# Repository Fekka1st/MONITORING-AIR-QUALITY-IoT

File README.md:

# Monitoring Air Quality and Smoke Emissions at Urban Bus Stops
_Ini adalah sebuah proyek untuk memonitoring kualitas udara di halte bus dengan menggunakan perangkat yaitu MQ135 dan juga MQ2 untuk mendeteksi ASAP_
_Sistem ini sudah integrasi dengan bylnk jadi kita bisa memantau melalui aplikasi tersebut untuk melihat data_
<h1>Anggota Proyek: </h1>
<h4>1.Hamdi Sholahudin</h4>
<h4>2.Hendri Hananta Wahyu Wibowo</h4>
<h4>3.Abu Yazid Bustomi</h4>
<h4>4.Ferry Aditya Herman </h4>
<h4>5.Tu Bagus Dwi Fikri </h4>

## Gambar Hasil :
<h3>Dashboard Blynk</h3>
<p align="center"></p>
<h3>Mobile Blynk</h3>
<p align="center"></p>

<h3>Device Monitoring</h3>
<p align="center"></p>
<p align="center"></p>  
<p align="center"></p>  

## Fitur :
- Mendeteksi Emisi ASAP
- Mendeteksi Kualitas Udara
- Mendeteksi Temperatur dan juga Kelembapan
- Ada Respon Suara jika ada asap berlebih atau kebakaran
- Ada led indikator untuk melihat kualitas udara (Green, Yellow, Red)
- Mendeteksi Lokasi Prangkat

## Requirements Prangkat :
- MQ2
- MQ135
- DHT22
- ESP32
- Buzzer
- LED RGB
- GPS NEON 6

## Platform Yang digunakan:
- Blynk
- Arduino IDE
- Platform.io
  
## Contact :
-[GitHub](https://www.github.com/Fekka1st/)
-

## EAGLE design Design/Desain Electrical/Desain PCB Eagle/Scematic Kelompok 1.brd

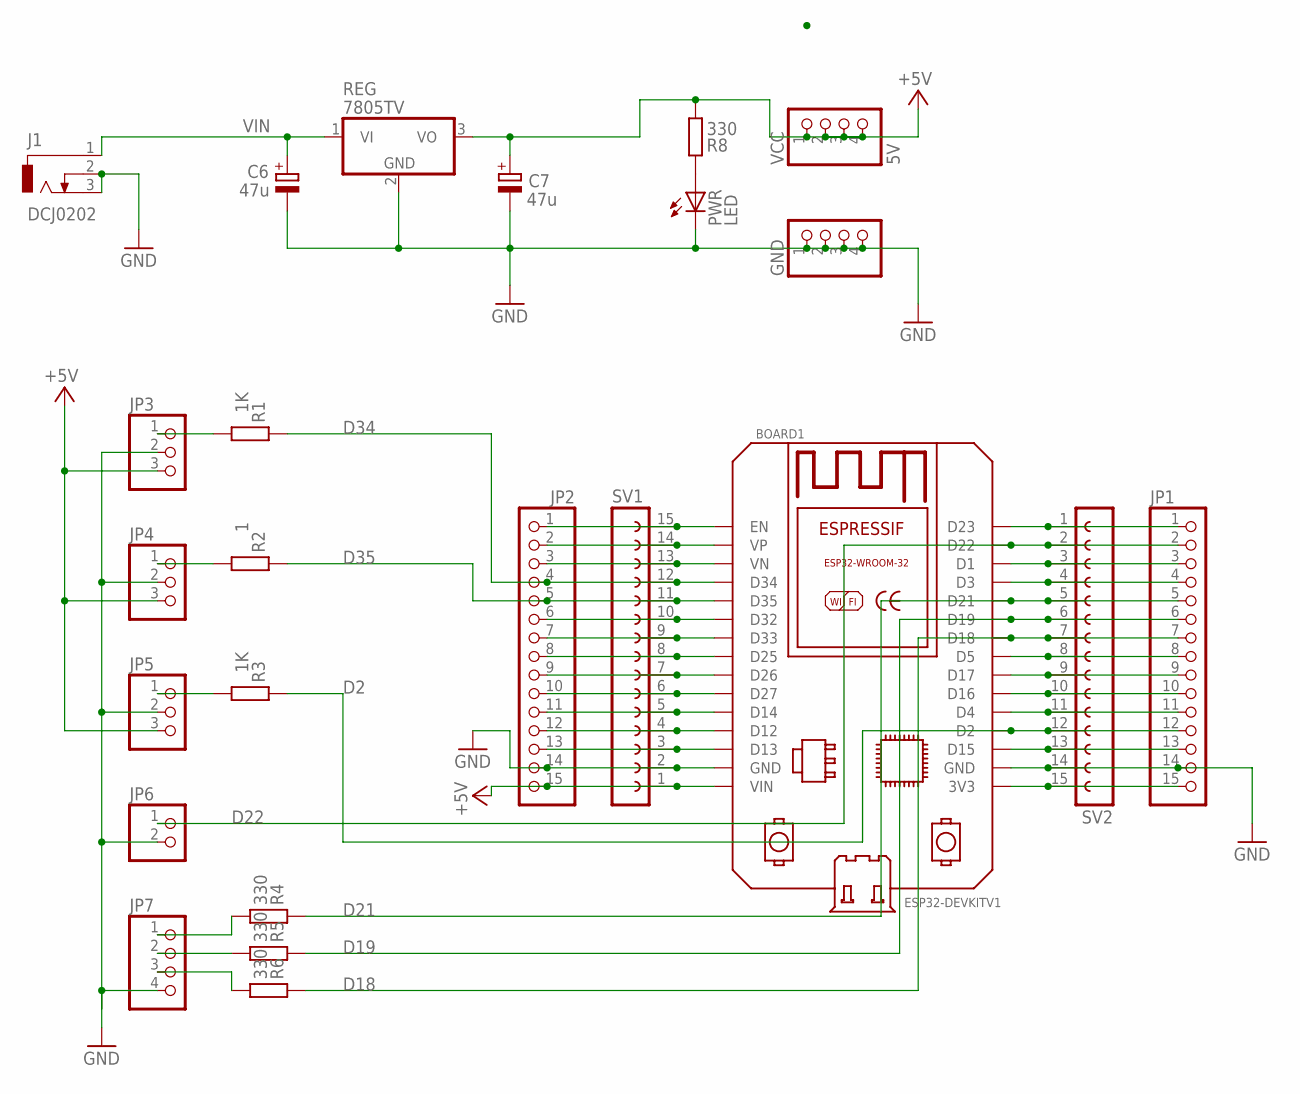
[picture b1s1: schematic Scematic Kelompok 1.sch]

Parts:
BOARD1: ESP32DEVKITV1SHRIDATTDUDHAT; ESP32-DEVKITV1
C6, C7: 47u; E2,5-5
GND: PINHD-1X4; 1X04
J1: DCJ0202
JP1, JP2: PINHD-1X15; 1X15
JP3, JP4, JP5: PINHD-1X3; 1X03
JP6: PINHD-1X2; 1X02
JP7: PINHD-1X4; 1X04
PWR: LED; LED3MM
R1, R3: 1K; 0204/7
R2: 1; 0204/7
R4, R5, R6, R8: 330; 0204/7
REG: 7805TV; TO220V
SV1, SV2: FE15-1; FE15
VCC: 5V; 1X04

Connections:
+5V: BOARD1.VIN, C7.+, JP2.15, JP3.3, JP4.3, JP5.3, R8.1, REG.3 (VO), SV1.1, VCC.1, VCC.2, VCC.3, VCC.4
D2: BOARD1.D2, JP1.12, R3.2, SV2.12
D18: BOARD1.D18, JP1.7, R6.2, SV2.7
D19: BOARD1.D19, JP1.6, R5.2, SV2.6
D21: BOARD1.D21, JP1.5, R4.2, SV2.5
D22: BOARD1.D22, JP1.2, JP6.1, SV2.2
D34: BOARD1.D34, JP2.4, R1.2, SV1.12
D35: BOARD1.D35, JP2.5, R2.2, SV1.11
GND: BOARD1.GND, BOARD1.GND@1 (GND), C6.-, C7.-, GND.1, GND.2, GND.3, GND.4, J1.2, J1.3, JP1.14, JP2.14, JP3.2, JP4.2, JP5.2, JP6.2, JP7.4, PWR.K (C), REG.2 (GND), SV1.2, SV2.14
unnamed: PWR.A, R8.2
unnamed: BOARD1.D26, JP2.9, SV1.7
unnamed: BOARD1.D33, BOARD1.EN, JP2.1, JP2.7, SV1.9, SV1.15
unnamed: BOARD1.VP, JP2.2, SV1.14
unnamed: BOARD1.VN, JP2.3, SV1.13
unnamed: BOARD1.D32, JP2.6, SV1.10
unnamed: BOARD1.D25, JP2.8, SV1.8
unnamed: BOARD1.D27, JP2.10, SV1.6
unnamed: BOARD1.D14, JP2.11, SV1.5
unnamed: BOARD1.D12, JP2.12, SV1.4
unnamed: BOARD1.D13, JP2.13, SV1.3
unnamed: JP3.1, R1.1
unnamed: BOARD1.D23, JP1.1, SV2.1
unnamed: BOARD1.D1, JP1.3, SV2.3
unnamed: BOARD1.D3, JP1.4, SV2.4
unnamed: BOARD1.D5, JP1.8, SV2.8
unnamed: BOARD1.D17, JP1.9, SV2.9
unnamed: BOARD1.D16, JP1.10, SV2.10
unnamed: BOARD1.D4, JP1.11, SV2.11
unnamed: BOARD1.D15, JP1.13, SV2.13
unnamed: JP4.1, R2.1
unnamed: BOARD1.3V3, JP1.15, SV2.15
unnamed: JP5.1, R3.1
unnamed: JP7.1, R4.1
unnamed: JP7.2, R5.1
unnamed: JP7.3, R6.1
VIN: C6.+, J1.1, REG.1 (VI)

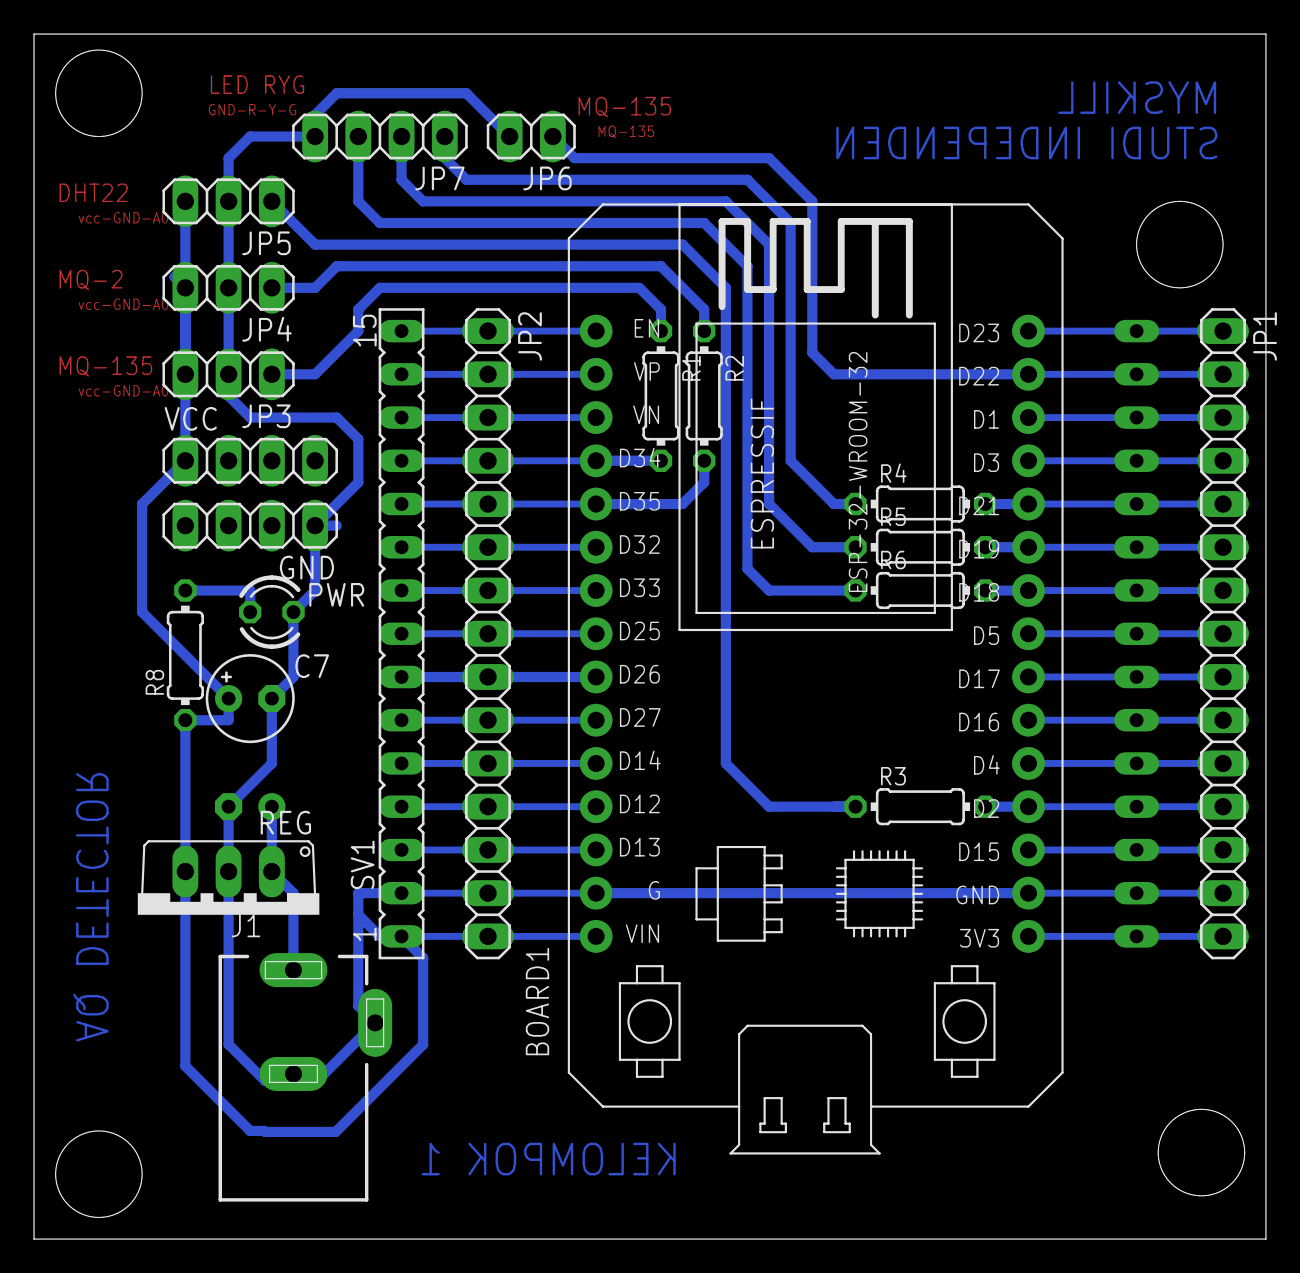
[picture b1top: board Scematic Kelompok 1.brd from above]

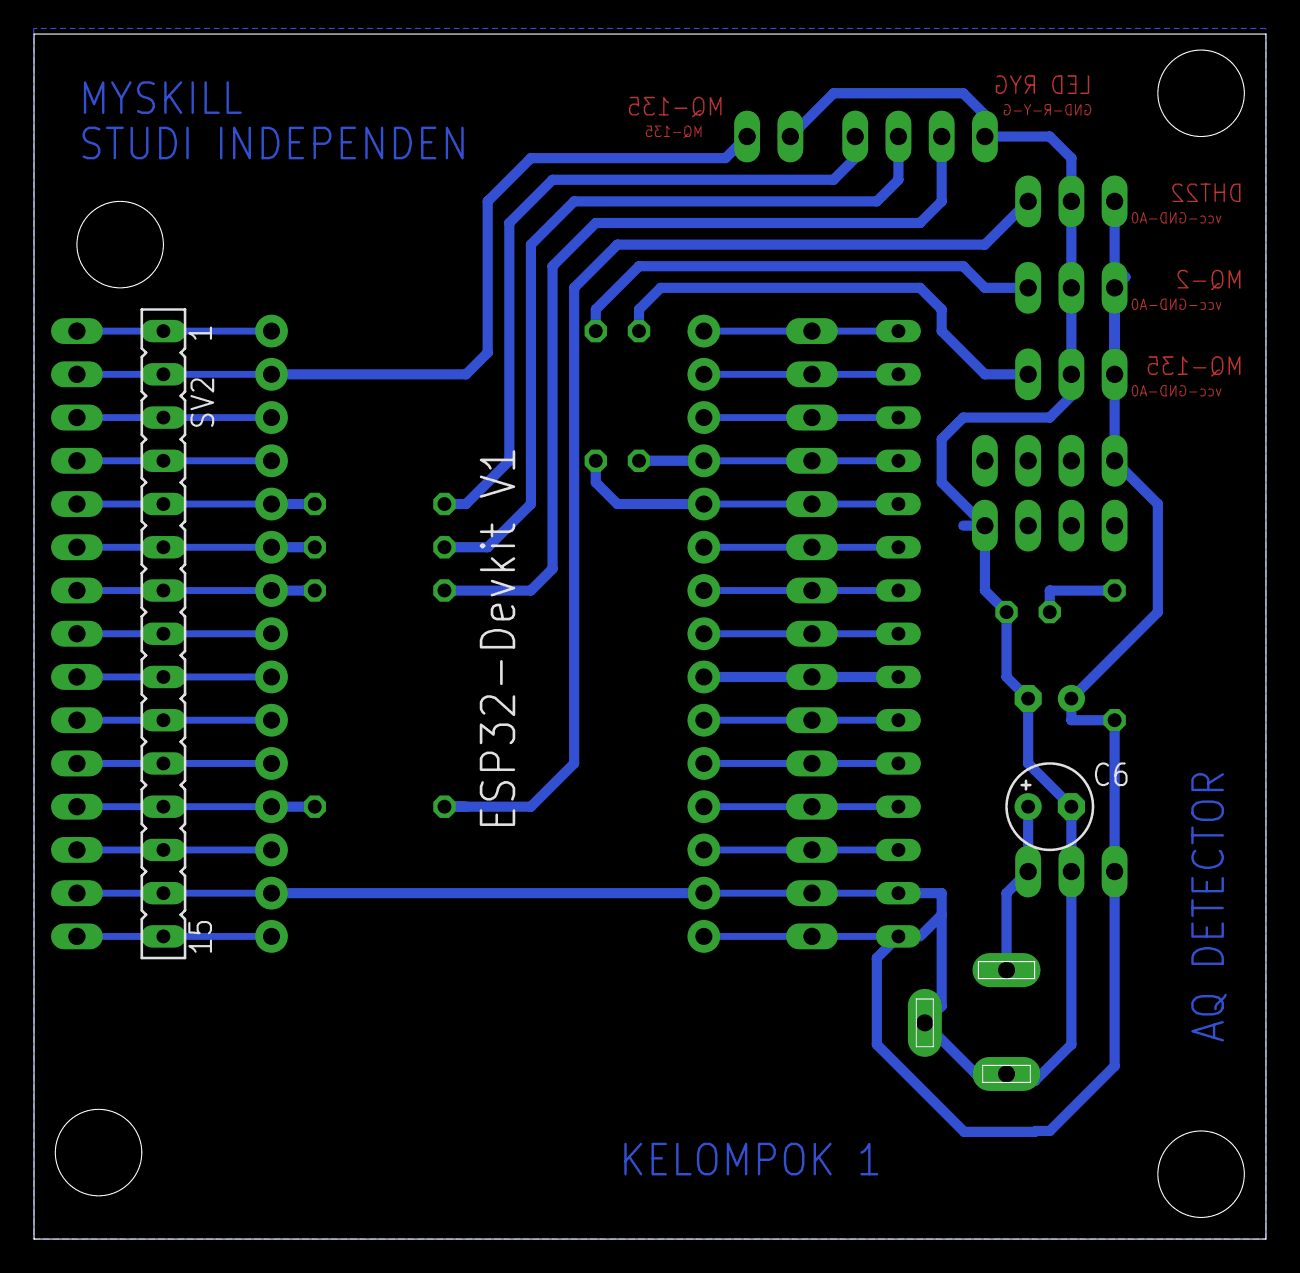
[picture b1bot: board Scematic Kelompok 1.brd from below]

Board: 2 copper layers, 72.4 x 70.8 mm, 24 parts (2 on the bottom side), 36 nets.

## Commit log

2023-06-09 Setup Awal
2023-06-09 #test
2023-06-11 #Code Semua Perangkat yang diperlukan
2023-06-11 #logic build
2023-06-12 #Nilai PPM belum stabil
2023-06-13 #Pengembangan #1
2023-06-13 #Pengembangan #2
2023-06-13 #Pengembangan 2
2023-06-13 Update README.md
    perubahan deskripsi
2023-06-13 #Pengembangan 3
2023-06-15 #V1.0
2023-06-15 #V1.1 Revisi
2023-06-18 #Final Revisi 2
2023-06-18 #Final Revisi 3
2023-06-18 #Penambahan Fitur GPS
2023-06-18 #Revisi Fix typo
2023-06-18 #revisi 3
2023-06-18 Create Design Hardware
    Desain Hardware
2023-06-18 update design
2023-06-19 #Penambahan Notifikasi Email dan Blynk
2023-06-20 #Fix Bug Blynk Maps
